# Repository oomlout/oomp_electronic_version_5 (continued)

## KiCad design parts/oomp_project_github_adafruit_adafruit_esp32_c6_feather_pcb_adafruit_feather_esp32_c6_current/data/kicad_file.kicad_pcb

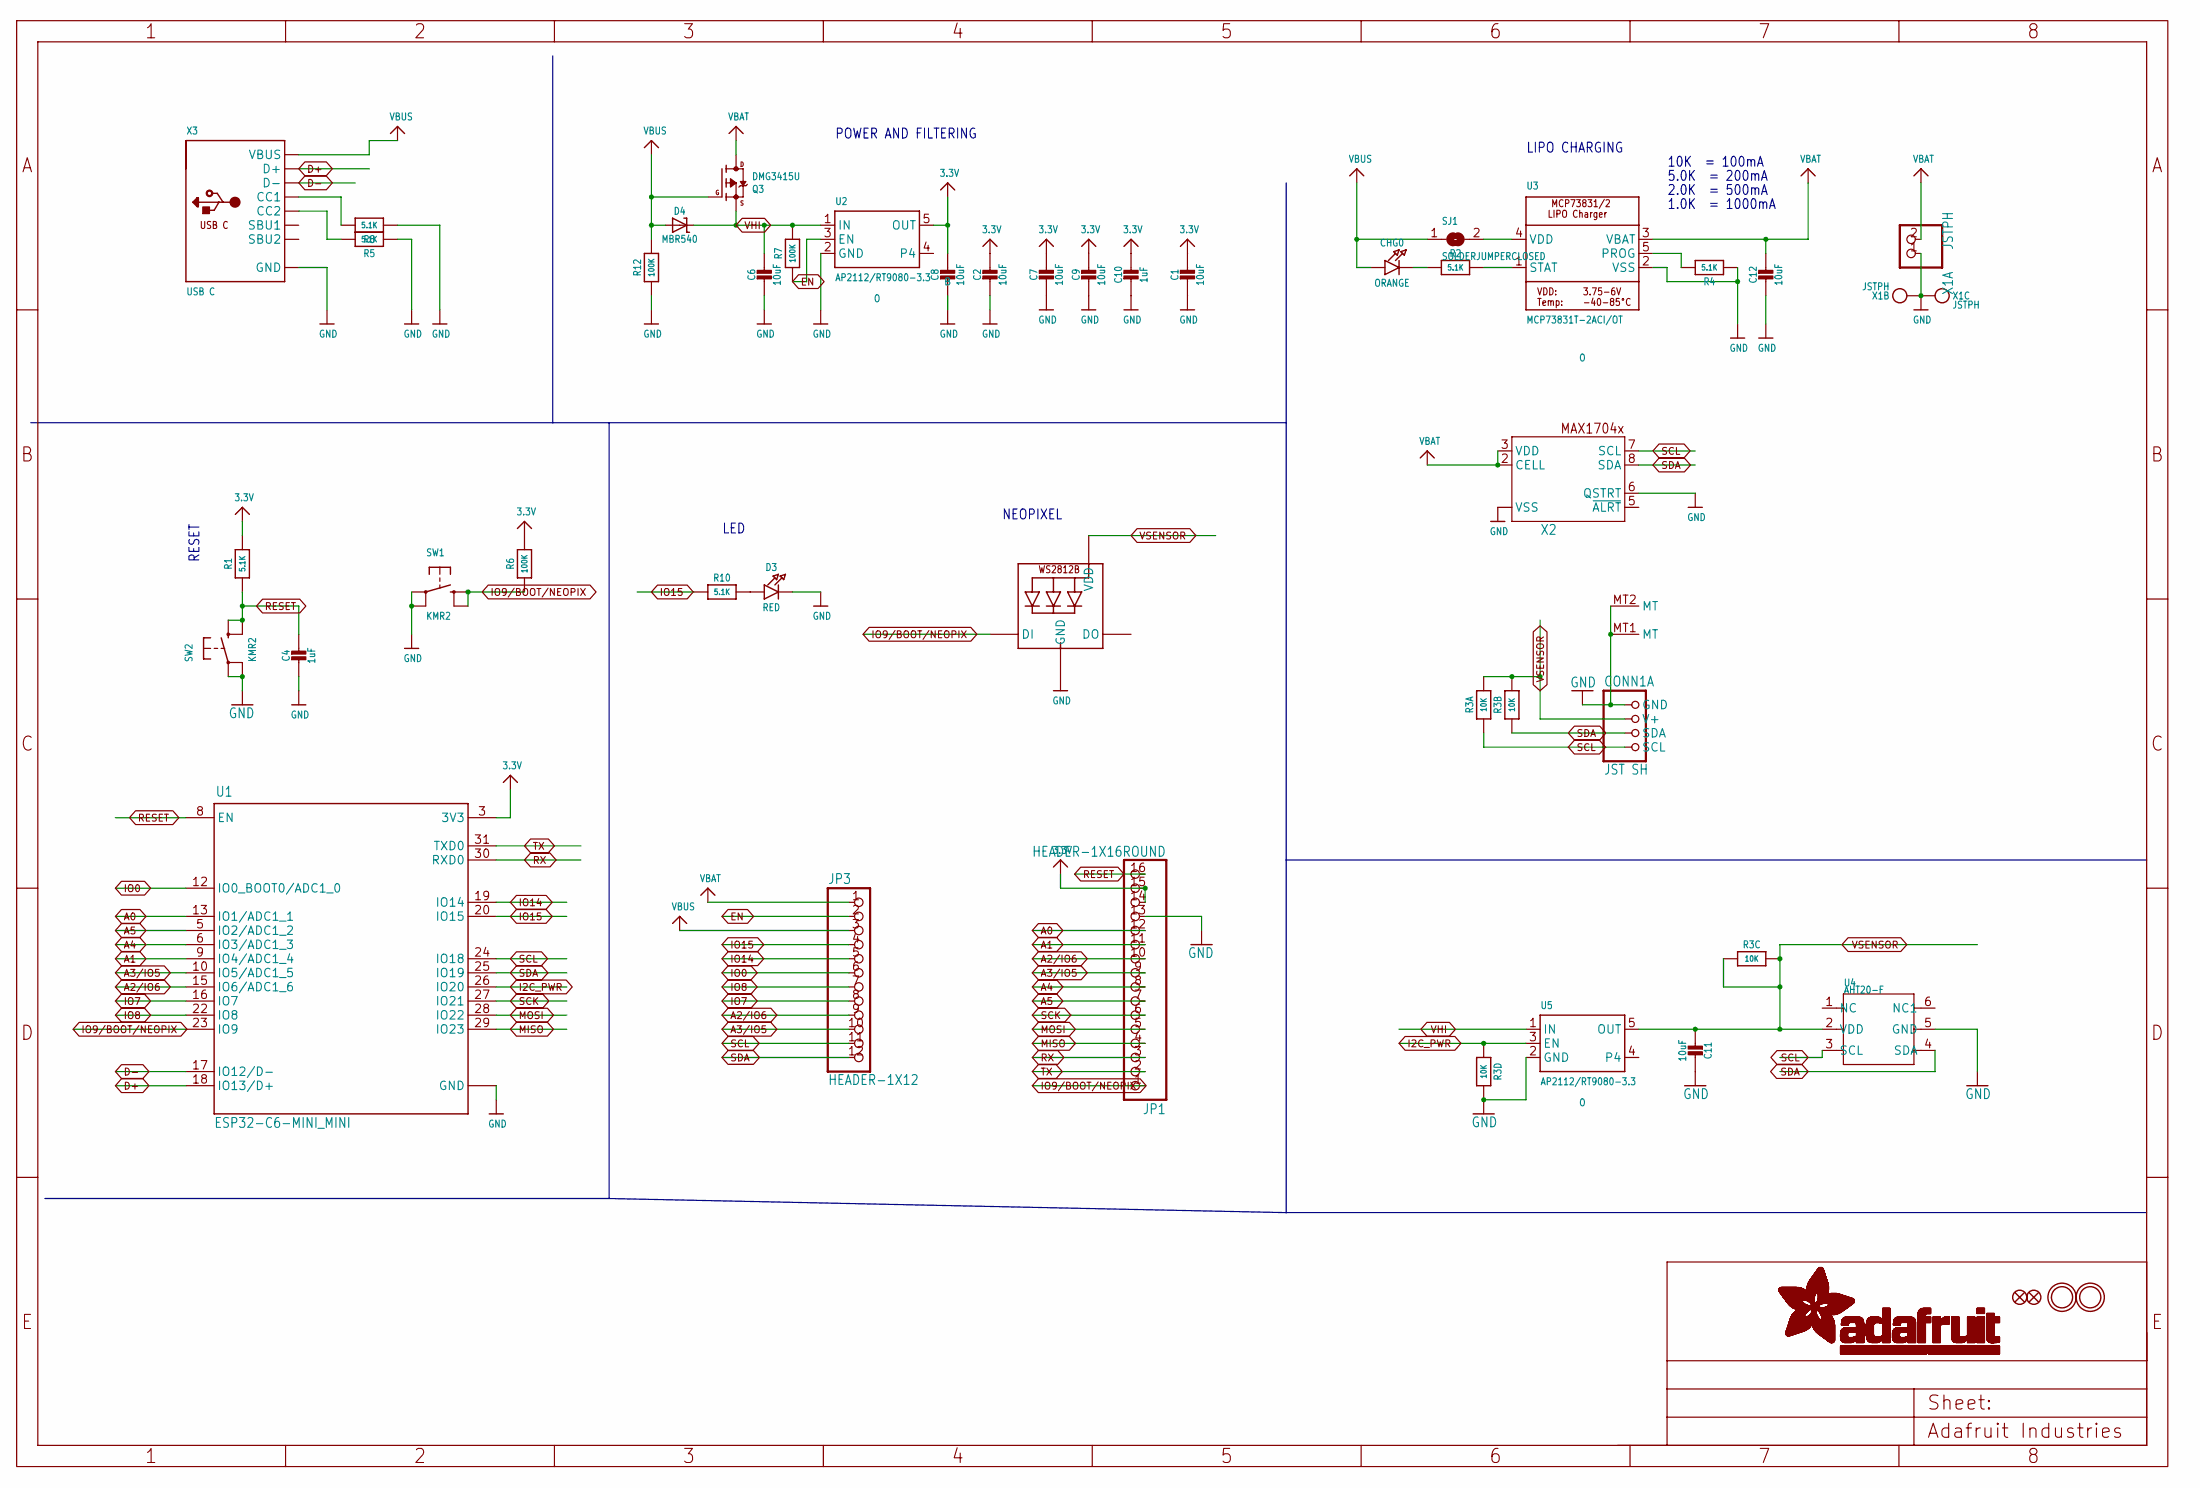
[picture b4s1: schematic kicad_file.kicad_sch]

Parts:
C1, C2, C6, C7, C8, C9, C11: 10uF; 0805-NO
C4, C10: 1uF; 0603-NO
C12: 10uF; _0805MP
CHG0: ORANGE; CHIPLED_0603_NOOUTLINE
CONN1: JST SH; JST_SH4_RA; LCSC C145961
D3: RED; CHIPLED_0603_NOOUTLINE
D4: MBR540; SOD-123
JP1: HEADER-1X16ROUND; 1X16_ROUND
JP3: HEADER-1X12; 1X12_ROUND
LED1: WS2812B_3535FULL; LED3535_FULLPADS
Q3: DMG3415U; SOT23-R
R1, R2, R4, R5, R8, R10: 5.1K; 0603-NO
R3: 10K; RESPACK_4X0603
R6, R7, R12: 100K; 0603-NO
SJ1: SOLDERJUMPERCLOSED; SOLDERJUMPER_CLOSEDWIRE
SW1, SW2: KMR2; BTN_RKB2_4.6X2.8
U1: ESP32-C6-MINI_MINI; ESP32-PICO-MINI
U2, U5: AP2112/RT9080-3.3; SOT23-5; JLC_ROTATION 0
U3: MCP73831T-2ACI/OT; SOT23-5; JLC_ROTATION 0
U4: AHT20-F; LONGAN-IC_SNR6-1.0-3X3X1MM; LCSC_PART C2757850
U$31, U$32: MOUNTINGHOLE2.5; MOUNTINGHOLE_2.5_PLATED
U$34, U$35: FIDUCIAL_1MM
X1: JSTPH; JSTPH2_BATT; LCSC C47647
X2: MAX17048/T; TDFN8_2X2MM
X3: USB C; USB_C_CUSB31-CFM2AX-01-X; LCSC C165948

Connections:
3.3V: C1.1, C2.1, C7.1, C8.1, C9.1, C10.1, JP1.14, JP1.15, R1.2, R6.2, U1.3 (3V3), U2.5 (OUT)
A0: JP1.12, U1.13 (IO1/ADC1_1)
A1: JP1.11, U1.9 (IO4/ADC1_4)
A2/IO6: JP1.10, JP3.9, U1.15 (IO6/ADC1_6)
A3/IO5: JP1.9, JP3.10, U1.10 (IO5/ADC1_5)
A4: JP1.8, U1.6 (IO3/ADC1_3)
A5: JP1.7, U1.5 (IO2/ADC1_2)
D+: U1.18 (IO13/D+), X3.A6 (D+), X3.B6 (D+)
D-: U1.17 (IO12/D-), X3.A7 (D-), X3.B7 (D-)
EN: JP3.2, R7.1, U2.3 (EN)
GND: C1.2, C2.2, C4.2, C6.2, C7.2, C8.2, C9.2, C10.2, C11.2, C12.2, CONN1.1 (GND), CONN1.MT1 (MT), CONN1.MT2 (MT), D3.C, JP1.13, LED1.4 (GND), R3.4 (1), R4.1, R5.1, R8.1, R12.1, SW1.A, SW1.A' (P1), SW2.A, SW2.A' (P1), U1.1 (GND), U1.2 (GND), U1.11 (GND), U1.14 (GND), U1.36 (GND), U1.37 (GND), U1.38 (GND), U1.39 (GND), U1.40 (GND), U1.41 (GND), U1.42 (GND), U1.43 (GND), U1.44 (GND), U1.45 (GND), U1.46 (GND), U1.47 (GND), U1.48 (GND), U1.49 (GND), U1.50 (GND), U1.51 (GND), U1.52 (GND), U1.53 (GND), U1.54 (GND), U1.55 (GND), U1.56 (GND), U1.57 (GND), U1.58 (GND), U1.59 (GND), U1.60 (GND), U1.61 (GND), U2.2 (GND), U3.2 (VSS), U4.5 (GND), U5.2 (GND), X1.1, X1.NC1, X1.NC2, X2.1 (VSS), X2.4 (VSS), X2.6 (QSTRT), X2.THERMAL (VSS), X3.A1B12 (GND), X3.B1A12 (GND)
I2C_PWR: R3.5 (2), U1.26 (IO20), U5.3 (EN)
IO0: JP3.6, U1.12 (IO0_BOOT0/ADC1_0)
IO7: JP3.8, U1.16 (IO7)
IO8: JP3.7, U1.22 (IO8)
IO9/BOOT/NEOPIX: JP1.1, LED1.1 (DI), R6.1, SW1.B (S), SW1.B' (S1), U1.23 (IO9)
IO14: JP3.5, U1.19 (IO14)
IO15: JP3.4, R10.1, U1.20 (IO15)
MISO: JP1.4, U1.29 (IO23)
MOSI: JP1.5, U1.28 (IO22)
unnamed: CHG0.C, R2.1
unnamed: SJ1.2, U3.4 (VDD)
unnamed: R2.2, U3.1 (STAT)
unnamed: R4.2, U3.5 (PROG)
unnamed: D3.A, R10.2
unnamed: R8.2, X3.A5 (CC1)
unnamed: R5.2, X3.B5 (CC2)
RESET: C4.1, JP1.16, R1.1, SW2.B (S), SW2.B' (S1), U1.8 (EN)
RX: JP1.3, U1.30 (RXD0)
SCK: JP1.6, U1.27 (IO21)
SCL: CONN1.4 (SCL), JP3.11, R3.1, U1.24 (IO18), U4.3 (SCL), X2.7 (SCL)
SDA: CONN1.3 (SDA), JP3.12, R3.2 (1), U1.25 (IO19), U4.4 (SDA), X2.8 (SDA)
TX: JP1.2, U1.31 (TXD0)
VBAT: C12.1, JP3.1, Q3.3 (D), U3.3 (VBAT), X1.2, X2.2 (CELL), X2.3 (VDD)
VBUS: CHG0.A, D4.A, JP3.3, Q3.1 (G), R12.2, SJ1.1, X3.A4B9 (VBUS), X3.B4A9 (VBUS)
VHI: C6.1, D4.C, Q3.2 (S), R7.2, U2.1 (IN), U5.1 (IN)
VSENSOR: C11.1, CONN1.2 (V+), LED1.2 (VDD), R3.3 (1), R3.6 (2), R3.7 (2), R3.8 (2), U4.2 (VDD), U5.5 (OUT)

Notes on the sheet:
RESET
5.0K = 200mA
10K = 100mA
1.0K = 1000mA
2.0K = 500mA
LIPO CHARGING
LED
POWER AND FILTERING
NEOPIXEL

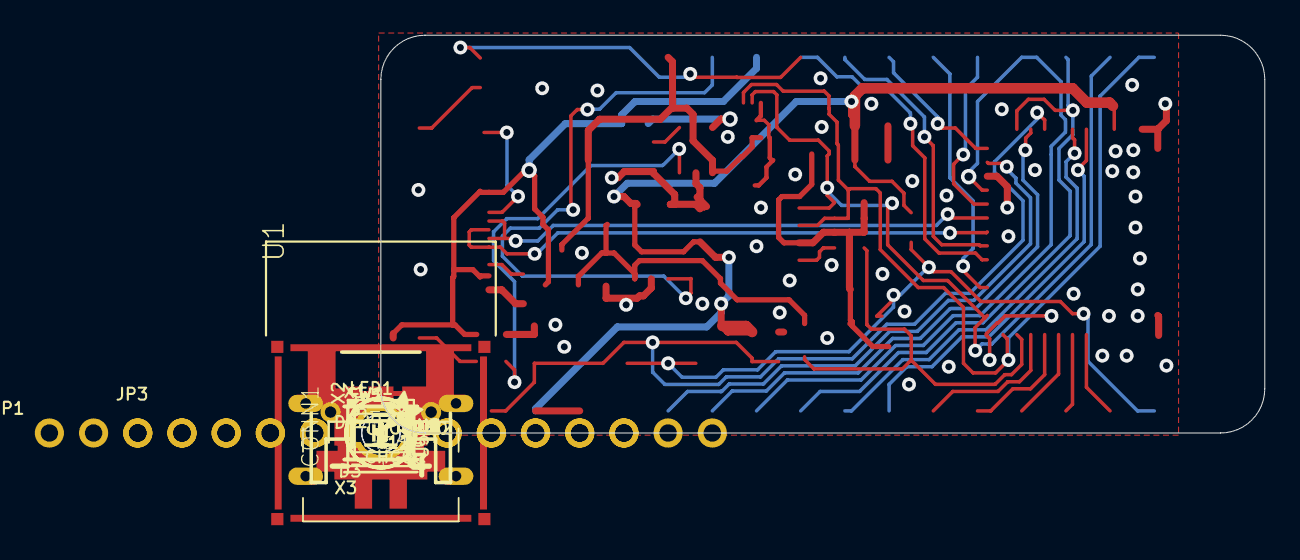
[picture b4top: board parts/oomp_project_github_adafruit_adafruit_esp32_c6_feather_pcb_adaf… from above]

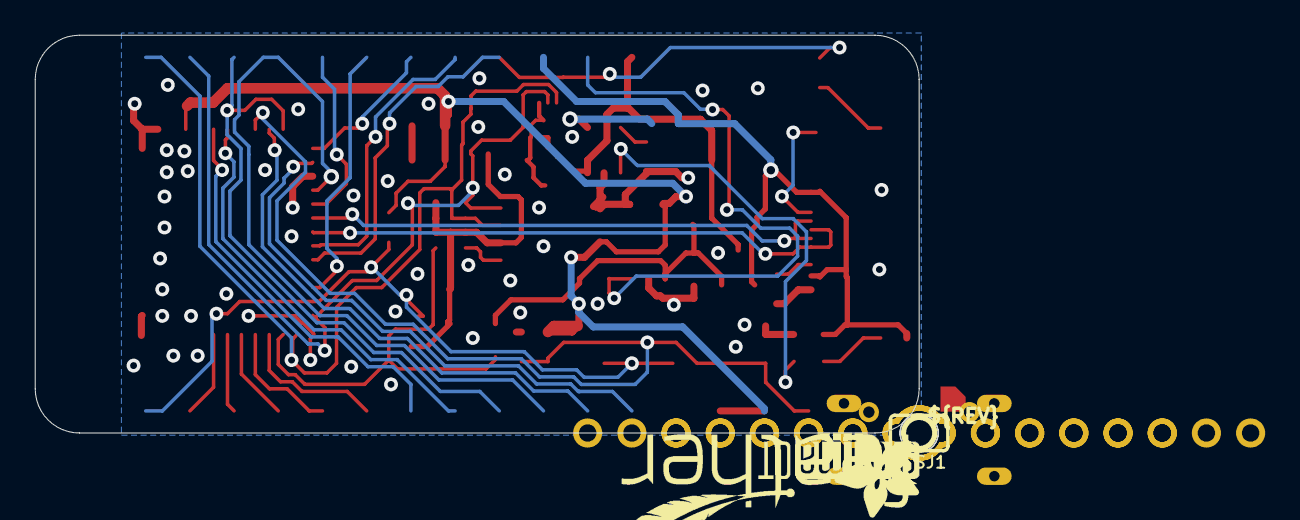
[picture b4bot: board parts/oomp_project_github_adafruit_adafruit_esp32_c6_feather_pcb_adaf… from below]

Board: 2 copper layers, 50.8 x 22.9 mm, 117 parts (36 on the bottom side), 37 nets.

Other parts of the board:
PLABEL0: PLABEL0
PLABEL1: PLABEL1
PLABEL2: PLABEL2
PLABEL4: PLABEL4
PLABEL5: PLABEL5
PLABEL6: PLABEL6
PLABEL7: PLABEL7
PLABEL8: PLABEL8
PLABEL9: PLABEL9
PLABEL10: PLABEL10
PLABEL11: PLABEL11
PLABEL12: PLABEL12
PLABEL13: PLABEL13
PLABEL14: PLABEL14
PLABEL15: PLABEL15
PLABEL16: PLABEL16
PLABEL17: PLABEL17
PLABEL18: PLABEL18
PLABEL19: PLABEL19
PLABEL20: PLABEL20
PLABEL21: PLABEL21
PLABEL22: PLABEL22
PLABEL23: PLABEL23
PLABEL24: PLABEL24
PLABEL25: PLABEL25
PLABEL26: PLABEL26
PLABEL27: PLABEL27
PLABEL28: PLABEL28
PLABEL29: PLABEL29
PLABEL30: PLABEL30
PLABEL31: PLABEL31
PLABEL32: PLABEL32
PLABEL33: PLABEL33
PLABEL34: PLABEL34
PLABEL35: PLABEL35
PLABEL36: PLABEL36
PLABEL37: PLABEL37
PLABEL38: PLABEL38
PLABEL39: PLABEL39
PLABEL40: PLABEL40
PLABEL41: PLABEL41
PLABEL42: PLABEL42
PLABEL43: PLABEL43
PLABEL44: PLABEL44
PLABEL45: PLABEL45
PLABEL46: PLABEL46
PLABEL47: PLABEL47
PLABEL48: PLABEL48
PLABEL49: PLABEL49
PLABEL51: PLABEL51
PLABEL52: PLABEL52
PLABEL53: PLABEL53
PLABEL54: PLABEL54
PLABEL55: PLABEL55
PLABEL56: PLABEL56
PLABEL57: PLABEL57
PLABEL58: PLABEL58
PLABEL59: PLABEL59
PLABEL60: PLABEL60
PLABEL61: PLABEL61
PLABEL62: PLABEL62
PLABEL63: PLABEL63
PLABEL64: PLABEL64
PLABEL65: PLABEL65
PLABEL66: PLABEL66
PLABEL67: PLABEL67
PLABEL68: PLABEL68
U$14: PCBFEAT-REV-040
U$15: FEATHERLOGO_MED
U$26: ADAFRUIT_2.5MM
U$48: ADAFRUIT_5MM
U$53: STEMMAQT
UNK_HOLE_0: dummyfp0
UNK_HOLE_1: dummyfp1

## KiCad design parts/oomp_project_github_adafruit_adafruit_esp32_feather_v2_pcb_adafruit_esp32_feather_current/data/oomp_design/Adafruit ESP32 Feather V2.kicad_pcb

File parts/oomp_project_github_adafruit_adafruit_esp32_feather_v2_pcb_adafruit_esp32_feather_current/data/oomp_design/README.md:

# OOMP KiCad design copy

Open `Adafruit ESP32 Feather V2.kicad_pro` (or the `.kicad_pcb` / `.kicad_sch`) in KiCad. Local OOMP libraries are under `libraries/`. Original inputs are preserved in [../original/](../original/).

Only verified unchanged installed KiCad defaults were renamed. Modified, custom, unmatched and unavailable items remain unchanged. Soldering variants are never swapped during conversion. Existing pad coordinates, nets and UUIDs are preserved.

See [conversion_report.yaml](conversion_report.yaml) for every conversion and skip. Copy this directory before editing; regeneration refuses to overwrite edited design files.

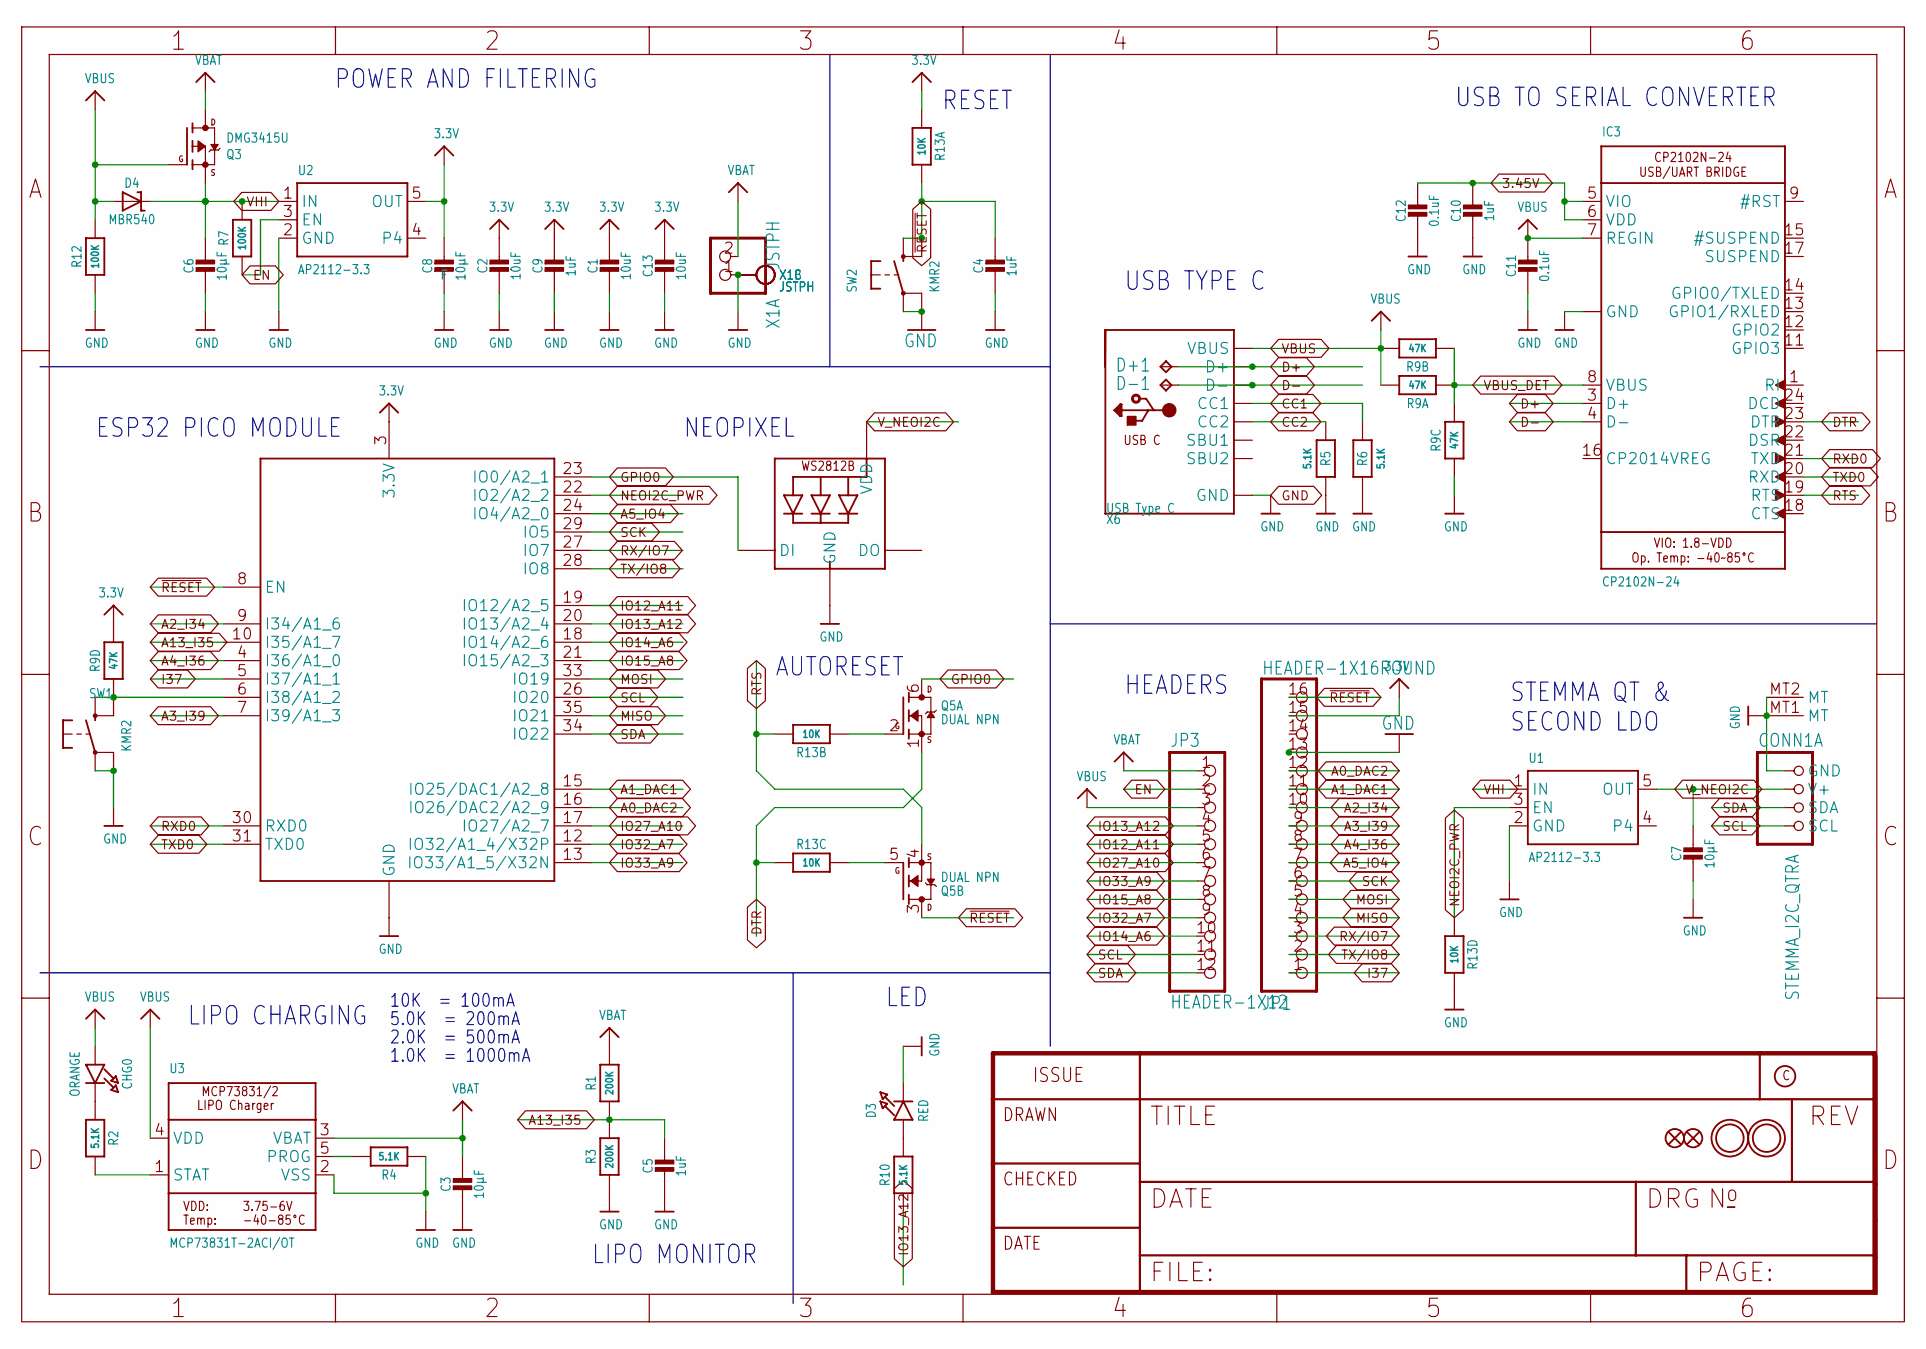
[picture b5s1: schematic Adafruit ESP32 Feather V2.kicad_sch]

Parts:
C1, C2, C13: 10uF; 0805-NO
C3, C6, C7, C8: 10µF; 0805-NO
C4, C5, C9, C10: 1uF; 0603-NO
C11, C12: 0.1uF; 0603-NO
CHG0: ORANGE; CHIPLED_0603_NOOUTLINE
CONN1: STEMMA_I2C_QTRA; JST_SH4_RA
D3: RED; CHIPLED_0603_NOOUTLINE
D4: MBR540; SOD-123
D+1: TPB1,27; B1,27
D-1: TPB1,27; B1,27
IC3: CP2102N-24; QFN24_4MM_SMSC
JP1: HEADER-1X16ROUND; 1X16_ROUND
JP3: HEADER-1X12; 1X12_ROUND
LED1: WS2812B3535; LED3535
Q3: DMG3415U; SOT23-R
Q5: DUAL NPN; SOT363
R1, R3: 200K; 0603-NO
R2, R4, R5, R6, R10: 5.1K; 0603-NO
R7, R12: 100K; 0603-NO
R9: 47K; RESPACK_4X0603
R13: 10K; RESPACK_4X0603
SW1, SW2: KMR2; BTN_KMR2_4.6X2.8
U1, U2: AP2112-3.3; SOT23-5
U3: MCP73831T-2ACI/OT; SOT23-5
U$31, U$32: MOUNTINGHOLE2.5; MOUNTINGHOLE_2.5_PLATED
U$34, U$35: FIDUCIAL_1MM
X1: JSTPH; JSTPH2_BATT
X3: ESP32-PICO-MINI-02MINI; ESP32-PICO-MINI
X6: USB Type C; USB_C_CUSB31-CFM2AX-01-X

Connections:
3.3V: C1.1, C2.1, C8.1, C9.1, C13.1, JP1.15, R9.5 (2), R13.1, U2.5 (OUT), X3.3 (3.3V)
3.45V: C10.1, C12.1, IC3.5 (VIO), IC3.6 (VDD)
A0_DAC2: JP1.12, X3.16 (IO26/DAC2/A2_9)
A1_DAC1: JP1.11, X3.15 (IO25/DAC1/A2_8)
A2_I34: JP1.10, X3.9 (I34/A1_6)
A3_I39: JP1.9, X3.7 (I39/A1_3)
A4_I36: JP1.8, X3.4 (I36/A1_0)
A5_IO4: JP1.7, X3.24 (IO4/A2_0)
A13_I35: C5.1, R1.1, R3.2, X3.10 (I35/A1_7)
CC1: R6.2, X6.A5 (CC1)
CC2: R5.2, X6.B5 (CC2)
D+: D+1.TP, IC3.3 (D+), X6.A6 (D+), X6.B6 (D+)
D-: D-1.TP, IC3.4 (D-), X6.A7 (D-), X6.B7 (D-)
DTR: IC3.23 (DTR), Q5.1 (S), R13.3 (1)
EN: JP3.2, R7.1, U2.3 (EN)
GND: C1.2, C2.2, C3.2, C4.2, C5.2, C6.2, C7.2, C8.2, C9.2, C10.2, C11.2, C12.2, C13.2, CONN1.1 (GND), CONN1.MT1 (MT), CONN1.MT2 (MT), D3.C, IC3.2 (GND), IC3.THERM (GND), JP1.13, LED1.4 (GND), R3.1, R4.1, R5.1, R6.1, R9.3 (1), R12.1, R13.5 (2), SW1.A, SW1.A' (P1), SW2.A, SW2.A' (P1), U1.2 (GND), U2.2 (GND), U3.2 (VSS), X1.1, X1.NC1, X1.NC2, X3.1 (GND), X3.2 (GND), X3.11 (GND), X3.14 (GND), X3.36 (GND), X3.37 (GND), X3.38 (GND), X3.39 (GND), X3.40 (GND), X3.41 (GND), X3.42 (GND), X3.43 (GND), X3.44 (GND), X3.45 (GND), X3.46 (GND), X3.47 (GND), X3.48 (GND), X3.49 (GND), X3.50 (GND), X3.51 (GND), X3.52 (GND), X3.53 (GND), X3.54 (GND), X3.55 (GND), X3.56 (GND), X3.57 (GND), X3.58 (GND), X3.59 (GND), X3.60 (GND), X3.61 (GND), X6.A1B12 (GND), X6.B1A12 (GND)
GPIO0: LED1.1 (DI), Q5.6 (D), X3.23 (IO0/A2_1)
I37: JP1.1, X3.5 (I37/A1_1)
IO12_A11: JP3.5, X3.19 (IO12/A2_5)
IO13_A12: JP3.4, R10.1, X3.20 (IO13/A2_4)
IO14_A6: JP3.10, X3.18 (IO14/A2_6)
IO15_A8: JP3.8, X3.21 (IO15/A2_3)
IO27_A10: JP3.6, X3.17 (IO27/A2_7)
IO32_A7: JP3.9, X3.12 (IO32/A1_4/X32P)
IO33_A9: JP3.7, X3.13 (IO33/A1_5/X32N)
MISO: JP1.4, X3.35 (IO21)
MOSI: JP1.5, X3.33 (IO19)
unnamed: CHG0.C, R2.1
unnamed: R2.2, U3.1 (STAT)
unnamed: R4.2, U3.5 (PROG)
unnamed: D3.A, R10.2
unnamed: R9.4 (1), SW1.B (S), SW1.B' (S1), X3.6 (I38/A1_2)
unnamed: Q5.5 (G), R13.6 (2)
unnamed: Q5.2 (G), R13.2 (1)
NEOI2C_PWR: R13.4 (1), U1.3 (EN), X3.22 (IO2/A2_2)
RTS: IC3.19 (RTS), Q5.4 (S), R13.7 (2)
RX/IO7: JP1.3, X3.27 (IO7)
RXD0: IC3.21 (TXD), X3.30 (RXD0)
SCK: JP1.6, X3.29 (IO5)
SCL: CONN1.4 (SCL), JP3.11, X3.26 (IO20)
SDA: CONN1.3 (SDA), JP3.12, X3.34 (IO22)
TX/IO8: JP1.2, X3.28 (IO8)
TXD0: IC3.20 (RXD), X3.31 (TXD0)
VBAT: C3.1, JP3.1, Q3.3 (D), R1.2, U3.3 (VBAT), X1.2
VBUS: C11.1, CHG0.A, D4.A, IC3.7 (REGIN), JP3.3, Q3.1 (G), R9.7 (2), R9.8 (2), R12.2, U3.4 (VDD), X6.A4B9 (VBUS), X6.B4A9 (VBUS)
VBUS_DET: IC3.8 (VBUS), R9.1, R9.2 (1), R9.6 (2)
VHI: C6.1, D4.C, Q3.2 (S), R7.2, U1.1 (IN), U2.1 (IN)
V_NEOI2C: C7.1, CONN1.2 (V+), LED1.2 (VDD), U1.5 (OUT)
~RESET: C4.1, JP1.16, Q5.3 (D), R13.8 (2), SW2.B (S), SW2.B' (S1), X3.8 (EN)

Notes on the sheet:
2.0K = 500mA
5.0K = 200mA
NEOPIXEL
USB TO SERIAL CONVERTER
RESET
1.0K = 1000mA
LIPO CHARGING
USB TYPE C
HEADERS
POWER AND FILTERING
10K = 100mA
ESP32 PICO MODULE
STEMMA QT & SECOND LDO
AUTORESET
LIPO MONITOR
LED

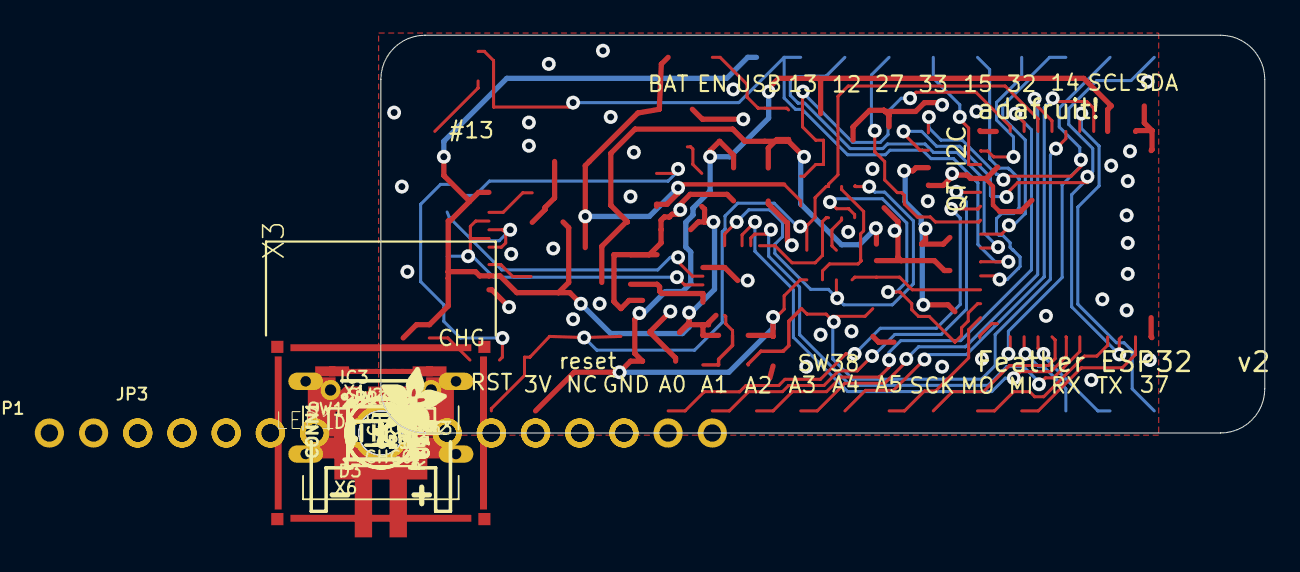
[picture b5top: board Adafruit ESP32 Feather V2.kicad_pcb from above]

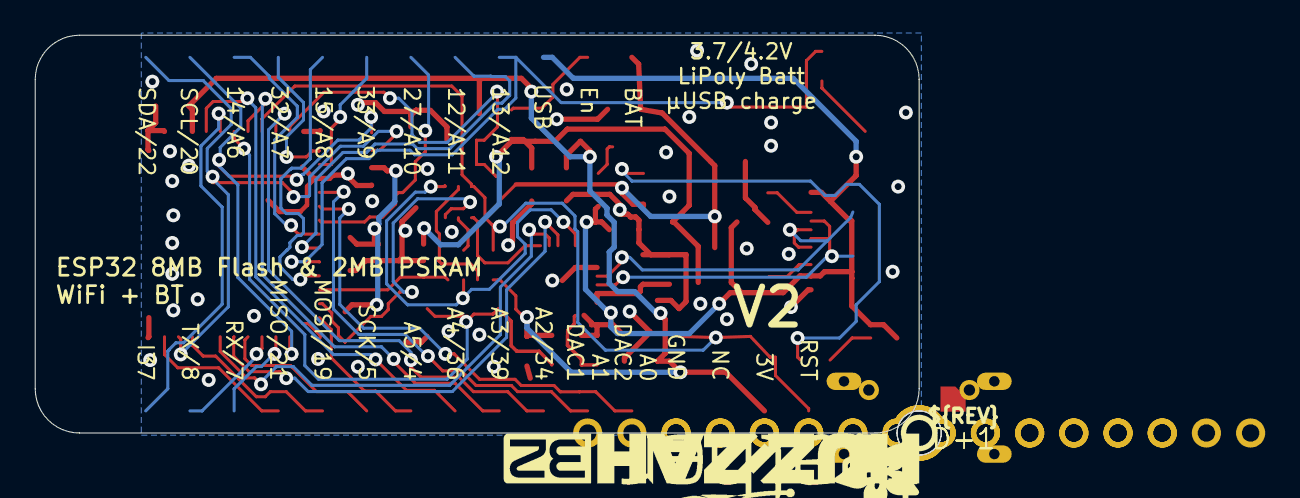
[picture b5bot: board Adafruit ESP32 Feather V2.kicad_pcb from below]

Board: 2 copper layers, 50.8 x 22.9 mm, 56 parts (6 on the bottom side), 49 nets.

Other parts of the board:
U$7: ADAFRUIT_5MM
U$9: FEATHERLOGO_MED
U$13: PCBFEAT-REV-040
U$14: ADAFRUIT_2.5MM
U$15: ADAFRUIT_3.5MM
U$43: HUZZAH32
UNK_HOLE_0: dummyfp0
UNK_HOLE_1: dummyfp1

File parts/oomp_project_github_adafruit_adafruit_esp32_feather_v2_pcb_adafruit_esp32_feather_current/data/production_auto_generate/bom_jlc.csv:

Comment,Designator,Footprint,LCSC Part #
,JP3,Adafruit ESP32 Feather V2-import-fps:1X12_ROUND,C7501588
,JP1,Adafruit ESP32 Feather V2-import-fps:1X16_ROUND,C7501270
,U$14,Adafruit ESP32 Feather V2-import-fps:ADAFRUIT_2.5MM,
,U$15,Adafruit ESP32 Feather V2-import-fps:ADAFRUIT_3.5MM,
,U$7,Adafruit ESP32 Feather V2-import-fps:ADAFRUIT_5MM,
,U$9,Adafruit ESP32 Feather V2-import-fps:FEATHERLOGO_MED,
,U$43,Adafruit ESP32 Feather V2-import-fps:HUZZAH32,
,U$13,Adafruit ESP32 Feather V2-import-fps:PCBFEAT-REV-040,
0.1uF,"C11,C12",Adafruit ESP32 Feather V2-import-fps:0603-NO,C14663
100K,"R7,R12",Adafruit ESP32 Feather V2-import-fps:0603-NO,C25803
10K,R13,Adafruit ESP32 Feather V2-import-fps:RESPACK_4X0603,C98220
10uF,"C1,C2,C13",Adafruit ESP32 Feather V2-import-fps:0805-NO,
10µF,"C3,C6,C7,C8",Adafruit ESP32 Feather V2-import-fps:0805-NO,
1uF,"C4,C5,C9,C10",Adafruit ESP32 Feather V2-import-fps:0603-NO,C5673
200K,"R1,R3",Adafruit ESP32 Feather V2-import-fps:0603-NO,
47K,R9,Adafruit ESP32 Feather V2-import-fps:RESPACK_4X0603,C2907042
5.1K,"R2,R4,R5,R6,R10",Adafruit ESP32 Feather V2-import-fps:0603-NO,C23186
AP2112-3.3,"U1,U2",Adafruit ESP32 Feather V2-import-fps:SOT23-5,
CP2102N-24,IC3,Adafruit ESP32 Feather V2-import-fps:QFN24_4MM_SMSC,
DMG3415U,Q3,Adafruit ESP32 Feather V2-import-fps:SOT23-R,
DUAL NPN,Q5,Adafruit ESP32 Feather V2-import-fps:SOT363,
ESP32-PICO-MINI-02MINI,X3,Adafruit ESP32 Feather V2-import-fps:ESP32-PICO-MINI,
FIDUCIAL_1MM,"U$34,U$35",Adafruit ESP32 Feather V2-import-fps:FIDUCIAL_1MM,
JSTPH,X1,Adafruit ESP32 Feather V2-import-fps:JSTPH2_BATT,
KMR2,"SW1,SW2",Adafruit ESP32 Feather V2-import-fps:BTN_KMR2_4.6X2.8,
MBR540,D4,Adafruit ESP32 Feather V2-import-fps:SOD-123,
MCP73831T-2ACI/OT,U3,Adafruit ESP32 Feather V2-import-fps:SOT23-5,
ORANGE,CHG0,Adafruit ESP32 Feather V2-import-fps:CHIPLED_0603_NOOUTLINE,
RED,D3,Adafruit ESP32 Feather V2-import-fps:CHIPLED_0603_NOOUTLINE,
STEMMA_I2C_QTRA,CONN1,Adafruit ESP32 Feather V2-import-fps:JST_SH4_RA,
"TPB1,27","D+1,D-1","Adafruit ESP32 Feather V2-import-fps:B1,27",
USB Type C,X6,Adafruit ESP32 Feather V2-import-fps:USB_C_CUSB31-CFM2AX-01-X,
WS2812B3535,LED1,Adafruit ESP32 Feather V2-import-fps:LED3535,
